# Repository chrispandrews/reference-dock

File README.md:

OpenXC Dock
===========

This repository is a part of the [OpenXC][] project.

This repository contains the documentation and open source design files for an
example OpenXC accessory dock, originally created by Ford.

The OpenXC Dock is a hub for connecting multiple USB accessories to an Android
tablet or phone. Since each accessory uses USB to communicate with the host, the
Dock is essentially a USB hub. The Dock receives power from the vehicle, and
regulates this power to a steady +5V for use by the accessory.

There is a [gallery of
photos](https://plus.google.com/photos/108408483770573977605/albums/5989365070748059233)
of the prototype dock.

### Buttons, Headers, Jumpers

*	JP2 - This jumper connects the +5V pin of the USB Micro connector to the +5V
	supply on the Dock. Connected by default. This enables charging of the
	Android device as well as standalone Dock usage with a PC.
*	SJ1 - USB hub reset - short this jumper to keep the USB hub in reset.
	Normally open.
*	SJ2 - Allows the USB hub to sense it's power state from the USB Micro
	connector. Normally closed by trace.
*	J10 - I2C - Exposes the i2c bus used by the USB hub for configuration
*	R35 - ID Resistor - For use with an Android device that expects a
	non-standard ID resistor in order to charge from USB OTG. The surface mount
	resistor R35 can be removed and a full-size 1/4W through hole resistor can
	be added instead.

### Known Issues

#### v0.3

*	USB D+ and D- swapped for downstream ports - An i2c EEPROM (AT24C02) was
	added to the board and soldered to J10. This allowed access to the PORT_SWAP
	register within the USB2517 hub, which enables the USB data lines to be
	swapped within the hub. Also
*	Downstream power ports are not enabled on hub poweron - The accessory USB
	connectors are not powered until a valid USB host has connected to the hub.
	Hub should be upgraded to a part with full Battery Charging support to
	enable this feature. The downstream power switches (U1, U2, U6, U7) were all
	reworked to remain permanently ON (each EN input trace was cut and the pin
	connected to +5V).
*	Downstream power ports will only flag a power fault when a host is
	connected. If an accessory malfunctions and draws too much power, the power
	switches will protect the accessory and Dock by limiting the current to
	500mA. When a host is connected, the LED for that port will light Red to
	indicate the fault. This does not occur when no host has been connected, so
	it's possible that a malfunctioning accessory will continue to draw ~500mA
	from the vehicle without alerting the user.

## License

Copyright (c) 2014 Ford Motor Company

The electrical and mechanical designs in this repository are available under the
[Creative Commons Attribution 4.0
International](http://creativecommons.org/licenses/by/4.0/deed.en_US) license.

[OpenXC]: http://openxcplatform.com

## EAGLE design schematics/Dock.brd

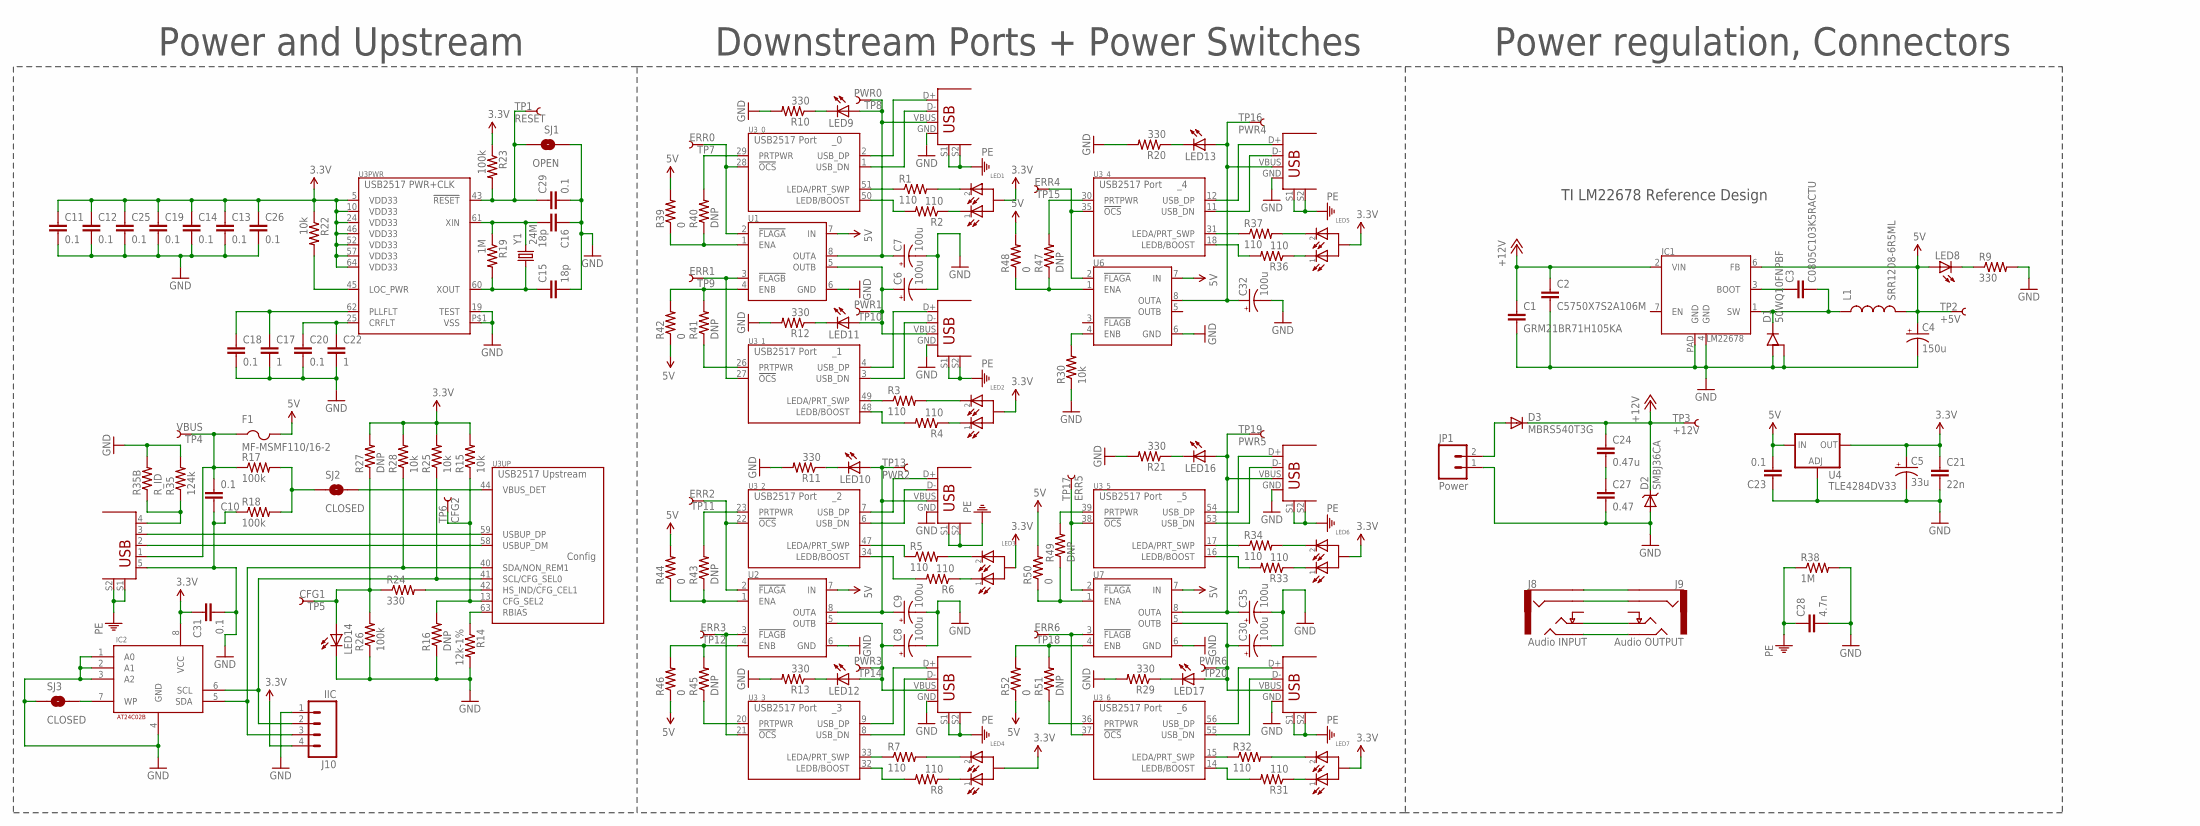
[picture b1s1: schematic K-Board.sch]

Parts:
C1: GRM21BR71H105KA; 0805
C2: C5750X7S2A106M; 2220
C3: C0805C103K5RACTU; 0805
C4: 150u; PANASONIC_D
C5: 33u; PANASONIC_C
C6, C7, C8, C9, C30, C32, C35: 100u; PANASONIC_D
C10, C11, C12, C13, C14, C18, C19, C20, C23, C25, C26, C29, C31: 0.1; 0402-CAP
C15, C16: 18p; 0402-CAP
C17, C22: 1; 0402-CAP
C21: 22n; 0402-CAP
C24: 0.47u; 0805
C27: 0.47; 0805
C28: 4.7n; 0805
D1: 50WQ10FNPBF; V-REG_DPACK
D2: SMBJ36CA; SMB-DIODE
D3: MBRS540T3G; SMC
F1: MF-MSMF110/16-2; 1812
IC1: LM22678; TO-263
IC2: ATMEL-AT24C02B-SS; SOIC8
J0: USB_MINIB_SHIELD-10118193; 10118193
J1, J2, J3, J4, J5, J6, J7: USB-A-S-RA-VERT; USB-A-TH-VERT
J8: Audio INPUT; SJ-4351X
J9: Audio OUTPUT; SJ-4351X
J10: IIC; 1X04
JP1: Power; 2-1445055-2
L1: SRR1208-6R5ML; SRR1208
LED1, LED2, LED3, LED4, LED5, LED6, LED7: LED_2X_COMMON_ANODE; LED_DUAL_3MMX1MM
LED8, LED9, LED10, LED11, LED12, LED13, LED14, LED16, LED17: LED0603; LED-0603
R1, R2, R3, R4, R5, R6, R7, R8, R31, R32, R33, R34, R36, R37: 110; 0402-RES
R9, R10, R11, R12, R13, R20, R21, R24, R29: 330; 0402-RES
R14: 12k-1%; 0402-RES
R15, R22, R25, R28, R30: 10k; 0402-RES
R16, R27, R40, R41, R43, R45, R47, R49, R51: DNP; 0402-RES
R17, R18, R23, R26: 100k; 0402-RES
R19: 1M; 0402-RES
R35: 124k; 0402-RES
R35B: R_ID; AXIAL-0.4
R38: 1M; 0805
R39, R42, R44, R46, R48, R50, R52: 0; 0402-RES
SJ1: OPEN; SJ_2S-NO
SJ2, SJ3: CLOSED; SJ_2S-TRACE
TP1: RESET; PAD.03X.03
TP2: +5V; PAD.03X.03
TP3: +12V; PAD.03X.03
TP4: VBUS; PAD.03X.03
TP5: CFG1; PAD.03X.03
TP6: CFG2; PAD.03X.03
TP7: ERR0; PAD.03X.03
TP8: PWR0; PAD.03X.03
TP9: ERR1; PAD.03X.03
TP10: PWR1; PAD.03X.03
TP11: ERR2; PAD.03X.03
TP12: ERR3; PAD.03X.03
TP13: PWR2; PAD.03X.03
TP14: PWR3; PAD.03X.03
TP15: ERR4; PAD.03X.03
TP16: PWR4; PAD.03X.03
TP17: ERR5; PAD.03X.03
TP18: ERR6; PAD.03X.03
TP19: PWR5; PAD.03X.03
TP20: PWR6; PAD.03X.03
U1, U2, U6, U7: MIC2026; SOIC8
U3: USB2517; QFN-64-PAD
U4: TLE4284DV33; V-REG_DPACK
Y1: 24M; HC49USX

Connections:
3.3V: C5.+, C11.1, C12.1, C13.1, C14.1, C19.1, C21.1, C25.1, C26.1, C31.1, IC2.8 (VCC), J10.4, LED1.1 (A), LED2.1 (A), LED3.1 (A), LED4.1 (A), LED5.1 (A), LED6.1 (A), LED7.1 (A), R15.2, R22.1, R23.1, R25.2, R27.2, R28.2, U3.5 (VDD33), U3.10 (VDD33), U3.24 (VDD33), U3.46 (VDD33), U3.52 (VDD33), U3.57 (VDD33), U3.64 (VDD33), U4.4 (OUT)
5V: C4.+, C23.2, F1.2, IC1.6 (FB), L1.2, LED8.A, R39.2, R42.1, R44.2, R46.1, R48.2, R50.2, R52.1, TP2.P$1, U1.7 (IN), U2.7 (IN), U4.3 (IN), U6.7 (IN), U7.7 (IN)
+12V: C1.1, C2.1, C24.1, D2.C, D3.C, IC1.2 (VIN), TP3.P$1
ENB3: R45.2, R46.2, U2.4 (ENB)
ENB6: R51.2, R52.2, U7.4 (ENB)
GND: C1.2, C2.2, C4.-, C5.-, C6.-, C7.-, C8.-, C9.-, C10.1, C11.2, C12.2, C13.2, C14.2, C15.2, C16.1, C17.2, C18.2, C19.2, C20.2, C21.2, C22.2, C23.1, C25.2, C26.2, C27.2, C28.2, C29.2, C30.-, C31.2, C32.-, C35.-, D1.1 (A), D1.3 (A), D2.A, IC1.4 (GND), IC1.PAD (GND), IC2.1 (A0), IC2.2 (A1), IC2.3 (A2), IC2.4 (GND), J0.5 (GND), J1.GND, J2.GND, J3.GND, J4.GND, J5.GND, J6.GND, J7.GND, J10.1, JP1.1, LED14.C, R9.2, R10.2, R11.2, R12.2, R13.2, R14.2, R16.1, R18.1, R20.2, R21.2, R26.1, R29.2, R30.1, R35.2, R35B.P$2 (2), R38.2, SJ1.1, SJ3.1, U1.6 (GND), U2.6 (GND), U3.19 (TEST), U3.P$1 (VSS), U4.1 (ADJ), U6.6 (GND), U7.6 (GND)
J7: J7.D+, U3.56 (USB_DP)
unnamed: C20.1, C22.1, U3.25 (CRFLT)
unnamed: R22.2, U3.45 (LOC_PWR)
unnamed: C17.1, C18.1, U3.62 (PLLFLT)
unnamed: C29.1, R23.2, SJ1.2, TP1.P$1, U3.43 (!RESET)
unnamed: C15.1, R19.2, U3.60 (XOUT), Y1.P$1 (1)
unnamed: C16.2, R19.1, U3.61 (XIN), Y1.P$2 (2)
unnamed: R30.2, U6.4 (ENB)
unnamed: R17.2, R18.2, SJ2.1
unnamed: J1.D-, U3.1 (USB_DN)
unnamed: SJ2.2, U3.44 (VBUS_DET)
unnamed: C10.2, F1.1, J0.1 (VBUS), R17.1, TP4.P$1
unnamed: R14.1, U3.63 (RBIAS)
unnamed: J1.D+, U3.2 (USB_DP)
unnamed: R2.2, U3.50 (LEDB/BOOST)
unnamed: R1.1, U3.51 (LEDA/PRT_SWP)
unnamed: LED1.3 (C2), R1.2
unnamed: LED1.2 (C1), R2.1
unnamed: TP7.P$1, U1.2 (!FLAGA), U3.28 (!OCS)
unnamed: R40.2, U3.29 (PRTPWR)
unnamed: C7.+, J1.VBUS, LED9.A, TP8.P$1, U1.8 (OUTA)
unnamed: R41.1, U3.26 (PRTPWR)
unnamed: TP9.P$1, U1.3 (!FLAGB), U3.27 (!OCS)
unnamed: J2.D-, U3.3 (USB_DN)
unnamed: J2.D+, U3.4 (USB_DP)
unnamed: C6.+, J2.VBUS, LED11.A, TP10.P$1, U1.5 (OUTB)
unnamed: LED2.3 (C2), R3.2
unnamed: R4.2, U3.48 (LEDB/BOOST)
unnamed: R3.1, U3.49 (LEDA/PRT_SWP)
unnamed: LED2.2 (C1), R4.1
unnamed: J6.D-, U3.53 (USB_DN)
unnamed: J3.D-, U3.6 (USB_DN)
unnamed: J3.D+, U3.7 (USB_DP)
unnamed: R6.2, U3.34 (LEDB/BOOST)
unnamed: R5.1, U3.47 (LEDA/PRT_SWP)
unnamed: LED3.3 (C2), R5.2
unnamed: LED3.2 (C1), R6.1
unnamed: LED11.C, R12.1
unnamed: J4.D-, U3.8 (USB_DN)
unnamed: J4.D+, U3.9 (USB_DP)
unnamed: C8.+, J4.VBUS, LED12.A, TP14.P$1, U2.5 (OUTB)
unnamed: LED4.3 (C2), R7.2
unnamed: R8.2, U3.32 (LEDB/BOOST)
unnamed: R7.1, U3.33 (LEDA/PRT_SWP)
unnamed: LED4.2 (C1), R8.1
unnamed: TP11.P$1, U2.2 (!FLAGA), U3.22 (!OCS)
unnamed: R43.2, U3.23 (PRTPWR)
unnamed: D3.A, JP1.2
unnamed: TP12.P$1, U2.3 (!FLAGB), U3.21 (!OCS)
unnamed: J5.D-, U3.11 (USB_DN)
unnamed: J5.D+, U3.12 (USB_DP)
unnamed: R36.2, U3.18 (LEDB/BOOST)
unnamed: R37.1, U3.31 (LEDA/PRT_SWP)
unnamed: LED5.3 (C2), R37.2
unnamed: LED5.2 (C1), R36.1
unnamed: C32.+, J5.VBUS, LED13.A, TP16.P$1, U6.8 (OUTA)
unnamed: J6.D+, U3.54 (USB_DP)
unnamed: R33.2, U3.16 (LEDB/BOOST)
unnamed: R34.1, U3.17 (LEDA/PRT_SWP)
unnamed: LED6.3 (C2), R34.2
unnamed: LED6.2 (C1), R33.1
unnamed: C35.+, J6.VBUS, LED16.A, TP19.P$1, U7.8 (OUTA)
unnamed: J7.D-, U3.55 (USB_DN)
unnamed: J8.3 (RING1), J9.3 (RING1)
unnamed: C30.+, J7.VBUS, LED17.A, TP20.P$1, U7.5 (OUTB)
unnamed: LED7.3 (C2), R32.2
unnamed: R31.2, U3.14 (LEDB/BOOST)
unnamed: R32.1, U3.15 (LEDA/PRT_SWP)
unnamed: LED7.2 (C1), R31.1
unnamed: TP15.P$1, U3.35 (!OCS), U6.2 (!FLAGA)
unnamed: R47.2, U3.30 (PRTPWR)
unnamed: TP17.P$1, U3.38 (!OCS), U7.2 (!FLAGA)
unnamed: R49.2, U3.39 (PRTPWR)
unnamed: TP18.P$1, U3.37 (!OCS), U7.3 (!FLAGB)
unnamed: R15.1, R16.2, TP6.P$1, U3.13 (CFG_SEL2)
unnamed: LED14.A, R24.1, R26.2, R27.1, TP5.P$1
unnamed: R24.2, U3.42 (HS_IND/CFG_CEL1)
unnamed: IC2.6 (SCL), J10.2, R25.1, U3.41 (SCL/CFG_SEL0)
unnamed: IC2.5 (SDA), J10.3, R28.1, U3.40 (SDA/NON_REM1)
unnamed: J8.2 (TIP), J9.2 (TIP)
unnamed: R39.1, R40.1, U1.1 (ENA)
unnamed: C3.1, IC1.3 (BOOT)
unnamed: J8.4 (RING2), J9.4 (RING2)
unnamed: J8.1 (SLEEVE), J9.1 (SLEEVE)
unnamed: LED8.C, R9.1
unnamed: LED9.C, R10.1
unnamed: C9.+, J3.VBUS, LED10.A, TP13.P$1, U2.8 (OUTA)
unnamed: LED10.C, R11.1
unnamed: C24.2, C27.1
unnamed: LED12.C, R13.1
unnamed: LED17.C, R29.1
unnamed: LED16.C, R21.1
unnamed: LED13.C, R20.1
unnamed: J0.4 (ID), R35.1, R35B.P$1 (1)
unnamed: R41.2, R42.2, U1.4 (ENB)
unnamed: R43.1, R44.1, U2.1 (ENA)
unnamed: R45.1, U3.20 (PRTPWR)
unnamed: R47.1, R48.1, U6.1 (ENA)
unnamed: R49.1, R50.1, U7.1 (ENA)
unnamed: R51.1, U3.36 (PRTPWR)
unnamed: IC2.7 (WP), SJ3.2
PE: C28.1, J0.S1, J0.S2, J1.S1, J1.S2, J2.S1, J2.S2, J3.S1, J3.S2, J4.S1, J4.S2, J5.S1, J5.S2, J6.S1, J6.S2, J7.S1, J7.S2, R38.1
SW: C3.2, D1.4 (C), IC1.1 (SW), L1.1
UP_DM: J0.2 (D-), U3.58 (USBUP_DM)
UP_DP: J0.3 (D+), U3.59 (USBUP_DP)

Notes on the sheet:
Power and Upstream
Downstream Ports + Power Switches
Power regulation, Connectors
TI LM22678 Reference Design

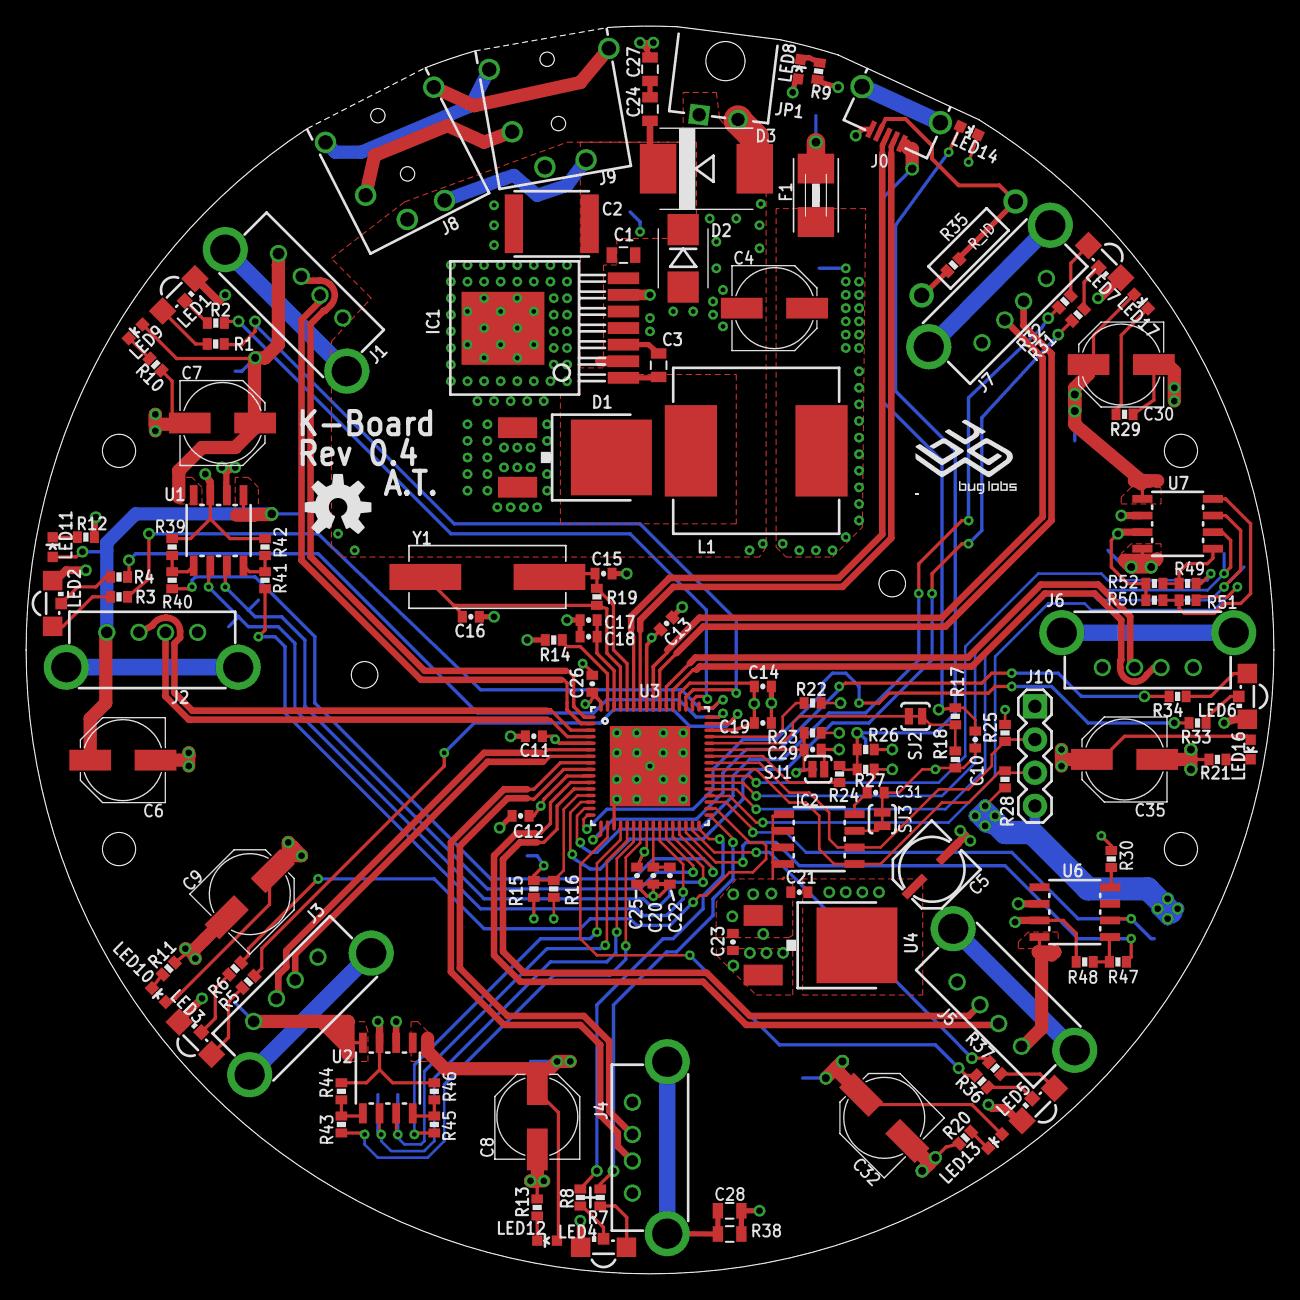
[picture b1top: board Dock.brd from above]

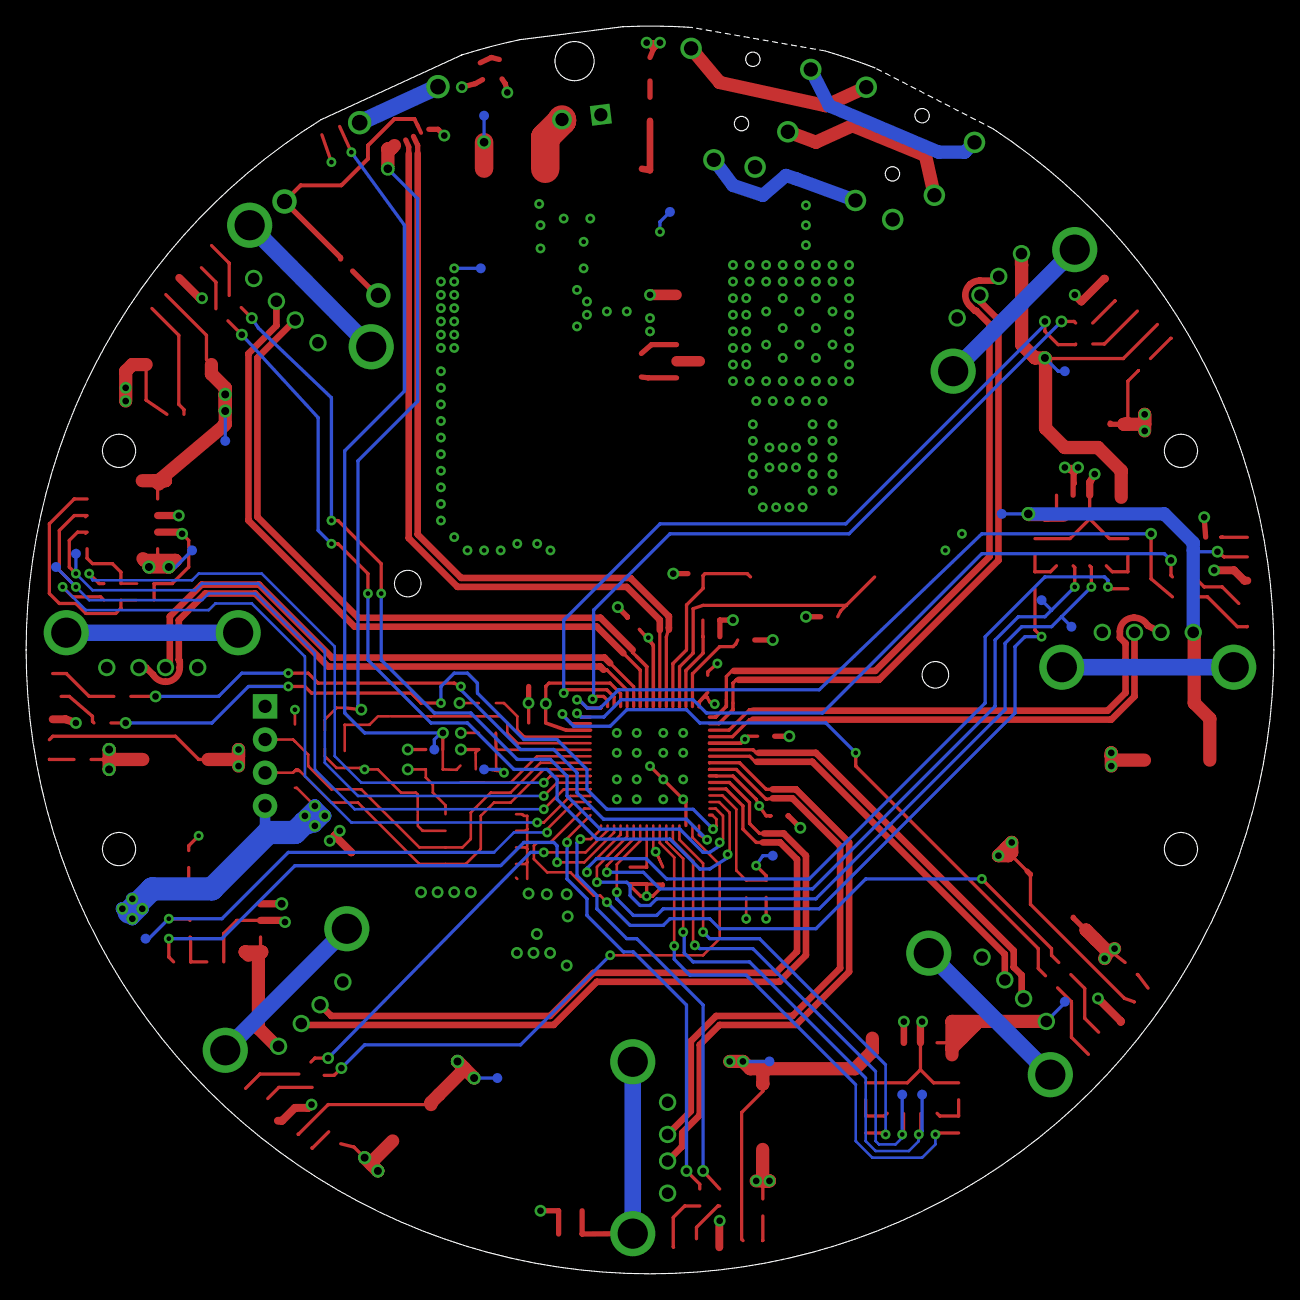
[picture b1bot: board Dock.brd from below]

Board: 4 copper layers, 95.5 x 95.5 mm, 155 parts (20 on the bottom side), 111 nets.

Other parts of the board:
DRILEGEND: DRILEGEND
SYM1: OSHW-LOGO-M
SYM2: BUG_LOGO_SM
U$9: A4L-LOC

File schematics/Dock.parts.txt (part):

Partlist

Exported from K-Board.sch at 3/12/13 11:59 AM

EAGLE Version 6.1.0 Copyright (c) 1988-2012 CadSoft

Assembly variant: 

Part     Value                     Device                    Package          Library               Sheet

C1       GRM21BR71H105KA           CAP0805                   0805             BUG                   1
C2       C5750X7S2A106M            CAP2220                   2220             BUG                   1
C3       C0805C103K5RACTU          CAP0805                   0805             BUG                   1
C4       150u                      CAP_POLD                  PANASONIC_D      BUG                   1
C5       33u                       CAP_POLC                  PANASONIC_C      BUG                   1
C6       100u                      CAP_POLD                  PANASONIC_D      BUG                   1
C7       100u                      CAP_POLD                  PANASONIC_D      BUG                   1
C8       100u                      CAP_POLD                  PANASONIC_D      BUG                   1
C9       100u                      CAP_POLD                  PANASONIC_D      BUG                   1
C10      0.1                       CAP0402-CAP               0402-CAP         BUG                   1
C11      0.1                       CAP0402-CAP               0402-CAP         BUG                   1
C12      0.1                       CAP0402-CAP               0402-CAP         BUG                   1
C13      0.1                       CAP0402-CAP               0402-CAP         BUG                   1
C14      0.1                       CAP0402-CAP               0402-CAP         BUG                   1
C15      18p                       CAP0402-CAP               0402-CAP         BUG                   1
C16      18p                       CAP0402-CAP               0402-CAP         BUG                   1
C17      1                         CAP0402-CAP               0402-CAP         BUG                   1
C18      0.1                       CAP0402-CAP               0402-CAP         BUG                   1
C19      0.1                       CAP0402-CAP               0402-CAP         BUG                   1
C20      0.1                       CAP0402-CAP               0402-CAP         BUG                   1
C21      22n                       CAP0402-CAP               0402-CAP         BUG                   1
C22      1                         CAP0402-CAP               0402-CAP         BUG                   1
C23      0.1                       CAP0402-CAP               0402-CAP         BUG                   1
C24      0.47u                     CAP0805                   0805             BUG                   1
C25      0.1                       CAP0402-CAP               0402-CAP         BUG                   1
C26      0.1                       CAP0402-CAP               0402-CAP         BUG                   1
C27      0.47                      CAP0805                   0805             BUG                   1
C28      4.7n                      CAP0805                   0805             BUG                   1
C29      0.1                       CAP0402-CAP               0402-CAP         BUG                   1
C30      100u                      CAP_POLD                  PANASONIC_D      BUG                   1
C31      0.1                       CAP0402-CAP               0402-CAP         BUG                   1
C32      100u                      CAP_POLD                  PANASONIC_D      BUG                   1
C35      100u                      CAP_POLD                  PANASONIC_D      BUG                   1
D1       50WQ10FNPBF               DIODE_COMMON_CAT-DPAK     V-REG_DPACK      BUG                   1
D2       SMBJ36CA                  DIODE-TVS-SMB             SMB-DIODE        BUG                   1
D3       MBRS540T3G                DIODESMC/DO-214AB         SMC              SparkFun-DiscreteSemi 1
F1       MF-MSMF110/16-2           PTCFUSE-1812              1812             adafruit              1
IC1      LM22678                   LM22678                   TO-263           BUG                   1
IC2      ATMEL-AT24C02B-SS         ATMEL-AT24C02B-SS         SOIC8            BUG                   1
J0       USB_MINIB_SHIELD-10118193 USB_MINIB_SHIELD-10118193 10118193         BUG                   1
J1       USB-A-S-RA-VERT           USB-A-S-RA-VERT           USB-A-TH-VERT    BUG                   1
J2       USB-A-S-RA-VERT           USB-A-S-RA-VERT           USB-A-TH-VERT    BUG                   1
J3       USB-A-S-RA-VERT           USB-A-S-RA-VERT           USB-A-TH-VERT    BUG                   1
J4       USB-A-S-RA-VERT           USB-A-S-RA-VERT           USB-A-TH-VERT    BUG                   1
J5       USB-A-S-RA-VERT           USB-A-S-RA-VERT           USB-A-TH-VERT    BUG                   1
J6       USB-A-S-RA-VERT           USB-A-S-RA-VERT           USB-A-TH-VERT    BUG                   1
J7       USB-A-S-RA-VERT           USB-A-S-RA-VERT           USB-A-TH-VERT    BUG                   1
J8       Audio INPUT               AUDIO-JACK-4PSWSJ-43515   SJ-4351X         BUG                   1
J9       Audio OUTPUT              AUDIO-JACK-4PSWSJ-43515   SJ-4351X         BUG                   1
J10      IIC                       M04PTH                    1X04             SparkFun-Connectors   1
JP1      Power                     M022-1445055-2            2-1445055-2      BUG                   1
L1       SRR1208-6R5ML             INDUCTORSRR1208           SRR1208          BUG                   1
LED1     LED_2X_COMMON_ANODE       LED_2X_COMMON_ANODE       LED_DUAL_3MMX1MM BUG                   1
LED2     LED_2X_COMMON_ANODE       LED_2X_COMMON_ANODE       LED_DUAL_3MMX1MM BUG                   1
LED3     LED_2X_COMMON_ANODE       LED_2X_COMMON_ANODE       LED_DUAL_3MMX1MM BUG                   1
LED4     LED_2X_COMMON_ANODE       LED_2X_COMMON_ANODE       LED_DUAL_3MMX1MM BUG                   1
LED5     LED_2X_COMMON_ANODE       LED_2X_COMMON_ANODE       LED_DUAL_3MMX1MM BUG                   1
LED6     LED_2X_COMMON_ANODE       LED_2X_COMMON_ANODE       LED_DUAL_3MMX1MM BUG                   1
LED7     LED_2X_COMMON_ANODE       LED_2X_COMMON_ANODE       LED_DUAL_3MMX1MM BUG                   1
LED8                               LED0603                   LED-0603         BUG                   1
LED9                               LED0603                   LED-0603         BUG                   1
LED10                              LED0603                   LED-0603         BUG                   1
LED11                              LED0603                   LED-0603         BUG                   1
LED12                              LED0603                   LED-0603         BUG                   1
LED13                              LED0603                   LED-0603         BUG                   1
LED14                              LED0603                   LED-0603         BUG                   1
LED16                              LED0603                   LED-0603         BUG                   1
LED17                              LED0603                   LED-0603         BUG                   1
R1       110                       RESISTOR0402-RES          0402-RES         BUG                   1
R2       110                       RESISTOR0402-RES          0402-RES         BUG                   1
R3       110                       RESISTOR0402-RES          0402-RES         BUG                   1
R4       110                       RESISTOR0402-RES          0402-RES         BUG                   1
R5       110                       RESISTOR0402-RES          0402-RES         BUG                   1
R6       110                       RESISTOR0402-RES          0402-RES         BUG                   1
R7       110                       RESISTOR0402-RES          0402-RES         BUG                   1
R8       110                       RESISTOR0402-RES          0402-RES         BUG                   1
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
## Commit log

2013-04-19 Initial commit.
2013-04-19 Update all K-board references to "Dock", including filenames.
    Also, remove references to iJoey and replace with "accessory".
2013-09-18 Add testing criteria as plaintext.
2013-09-18 Add iJoey design guidelines.
2013-09-18 Add a DFM consideration.
2014-03-11 Add license for release.
2014-03-11 Add link to photo gallery.

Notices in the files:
parts and their libraries:
SparkFun-Connectors: Licensing: CC v3.0 Share-Alike You are welcome to use this library for commercial purposes.
